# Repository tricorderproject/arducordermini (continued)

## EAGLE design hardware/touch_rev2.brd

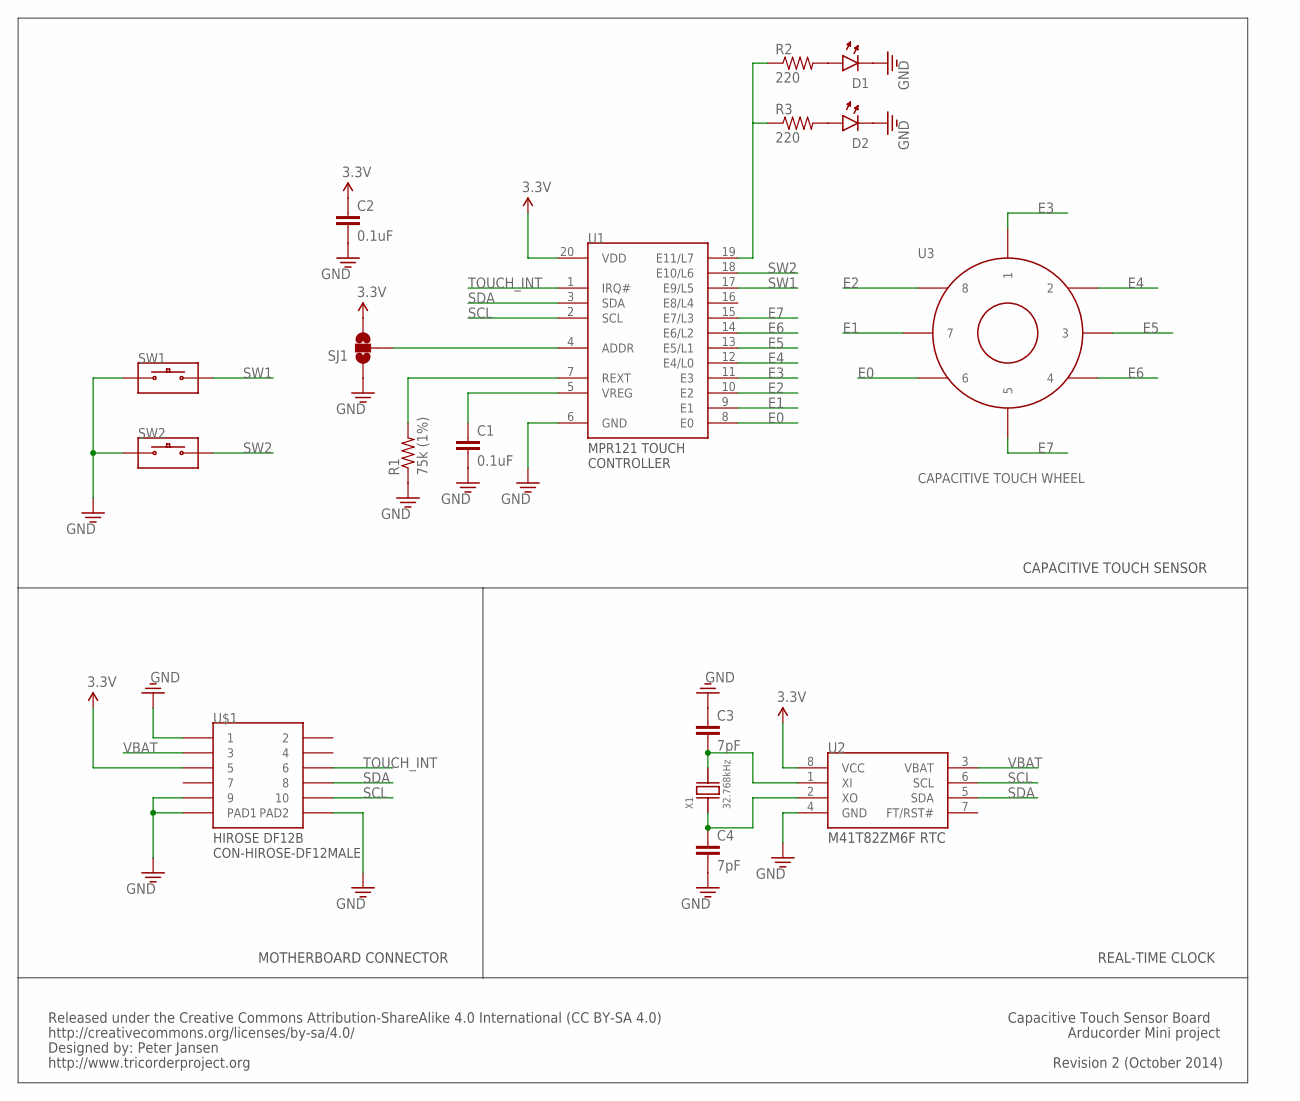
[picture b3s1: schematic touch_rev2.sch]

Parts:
C1, C2: 0.1uF; 0603
C3, C4: 7pF; 0603
D1, D2: 0605-LED; 0603-LED
R1: 75k (1%); 0603
R2, R3: 220; 0603
SJ1: SOLDERJUMPER_2WAYPASTE1&2; SJ_3_PASTE1&2
SW1, SW2: SWITCH; KMT071
U1: MPR121-TOUCH-CONTROLLER; QFN-3X3-20
U2: M41T82ZM6F; 8-SOIC
U3: CAPACITIVE-WHEEL-8
U$1: CON-HIROSE-DF12MALE; DF12B(3.0)-10DS-0.5V(86)
X1: 32.768kHz; CRYSTAL-9HT10

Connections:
3.3V: C2.1, SJ1.3, U1.20 (VDD), U2.8 (VCC), U$1.5
E0: U1.8 (E0), U3.6
E1: U1.9 (E1), U3.7
E2: U1.10 (E2), U3.8
E3: U1.11 (E3), U3.1
E4: U1.12 (E4/L0), U3.2
E5: U1.13 (E5/L1), U3.3
E6: U1.14 (E6/L2), U3.4
E7: U1.15 (E7/L3), U3.5
GND: C1.2, C2.2, C3.1, C4.2, D1.CATHODE, D2.CATHODE, R1.1, SJ1.1, SW1.1A, SW2.1A, U1.6 (GND), U2.4 (GND), U$1.1, U$1.9, U$1.PAD1, U$1.PAD2
unnamed: D1.ANODE, R2.2
unnamed: D2.ANODE, R3.2
unnamed: C1.1, U1.5 (VREG)
unnamed: R1.2, U1.7 (REXT)
unnamed: SJ1.2, U1.4 (ADDR)
unnamed: R2.1, R3.1, U1.19 (E11/L7)
unnamed: C4.1, U2.2 (XO), X1.1
unnamed: C3.2, U2.1 (XI), X1.2
SCL: U1.2 (SCL), U2.6 (SCL), U$1.10
SDA: U1.3 (SDA), U2.5 (SDA), U$1.8
SW1: SW1.2A, U1.17 (E9/L5)
SW2: SW2.2A, U1.18 (E10/L6)
TOUCH_INT: U1.1 (IRQ#), U$1.6
VBAT: U2.3 (VBAT), U$1.3

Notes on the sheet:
CAPACITIVE TOUCH SENSOR
REAL-TIME CLOCK
MOTHERBOARD CONNECTOR
Released under the Creative Commons Attribution-ShareAlike 4.0 International (CC BY-SA 4.0)
http://creativecommons.org/licenses/by-sa/4.0/
Designed by: Peter Jansen
http://www.tricorderproject.org
Revision 2 (October 2014)
Arducorder Mini project
Capacitive Touch Sensor Board

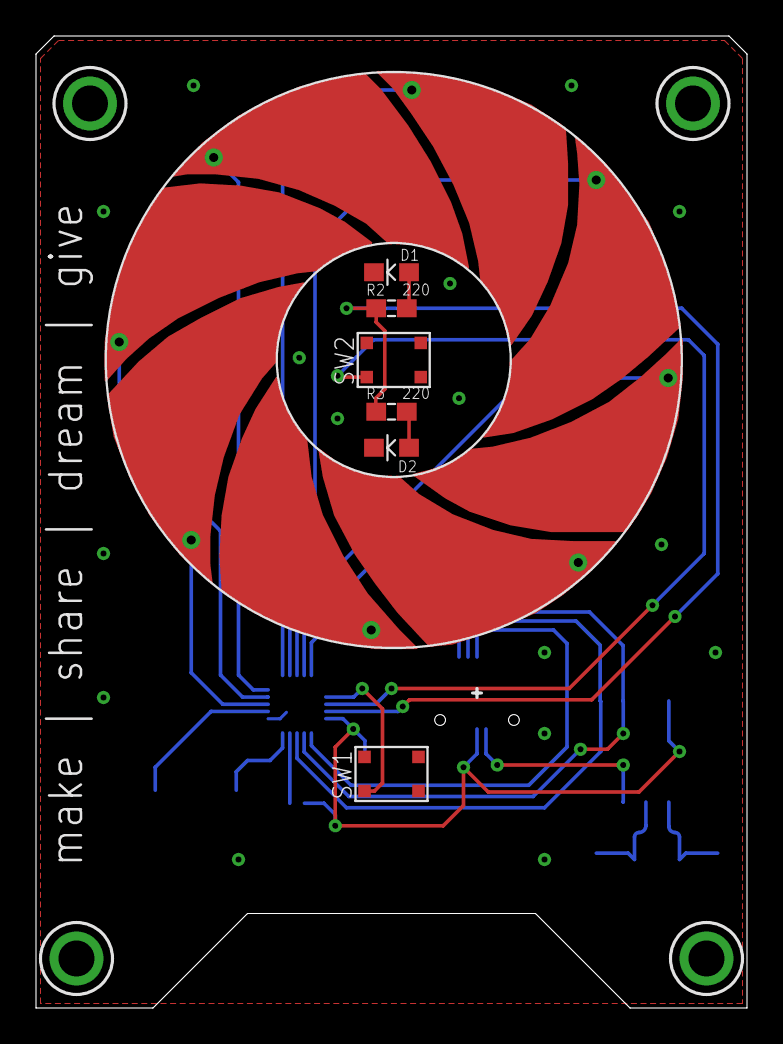
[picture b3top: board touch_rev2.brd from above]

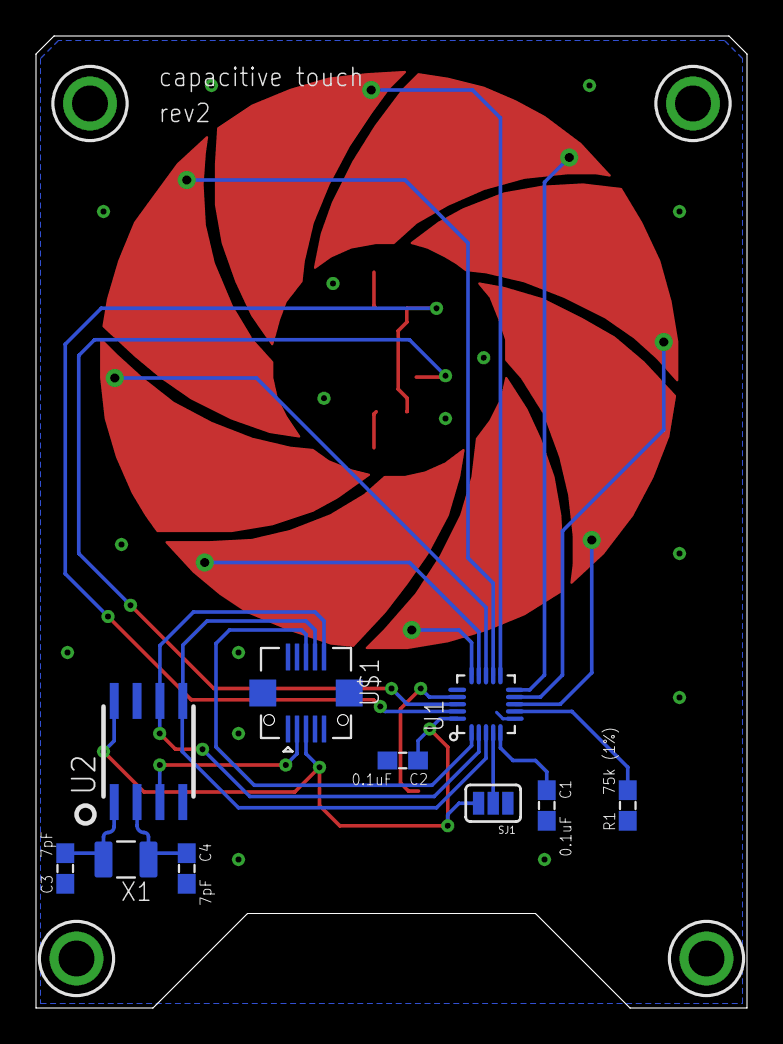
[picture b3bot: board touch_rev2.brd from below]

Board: 2 copper layers, 39.5 x 54.0 mm, 17 parts (9 on the bottom side), 24 nets.

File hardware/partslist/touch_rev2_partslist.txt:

Partlist

Exported from touch_rev2.sch at 27/10/2014 11:53:52 PM

EAGLE Version 6.5.0 Copyright (c) 1988-2013 CadSoft

Assembly variant: 

Part     Value                   Device                    Package                  Library               Sheet

C1       0.1uF                   CAP0603                   0603                     notes_mark5a          1
C2       0.1uF                   CAP0603                   0603                     notes_mark5a          1
C3       7pF                     CAP0603                   0603                     notes_mark5a          1
C4       7pF                     CAP0603                   0603                     notes_mark5a          1
D1       0605-LED                0605-LED                  0603-LED                 notes_mark5a1         1
D2       0605-LED                0605-LED                  0603-LED                 notes_mark5a1         1
R1       75k (1%)                RESISTOR0603              0603                     notes_mark5a1         1
R2       220                     RESISTOR0603              0603                     notes_mark5a1         1
R3       220                     RESISTOR0603              0603                     notes_mark5a1         1
SJ1                              SOLDERJUMPER_2WAYPASTE1&2 SJ_3_PASTE1&2            SparkFun-Passives     1
SW1      SWITCH                  SWITCH                    KMT071                   notes-arducorder-mini 1
SW2      SWITCH                  SWITCH                    KMT071                   notes-arducorder-mini 1
U$1      CON-HIROSE-DF12MALE     CON-HIROSE-DF12MALE       DF12B(3.0)-10DS-0.5V(86) arducorder-mini       1
U1       MPR121-TOUCH-CONTROLLER MPR121-TOUCH-CONTROLLER   QFN-3X3-20               notes-arducorder-mini 1
U2       M41T82ZM6F              M41T82ZM6F                8-SOIC                   notes_mark5a          1
U3       CAPACITIVE-WHEEL-8      CAPACITIVE-WHEEL-8        CAPACITIVE-WHEEL-8       notes-arducorder-mini 1
X1       32.768kHz               CRYSTAL                   CRYSTAL-9HT10            notes_mark5a          1

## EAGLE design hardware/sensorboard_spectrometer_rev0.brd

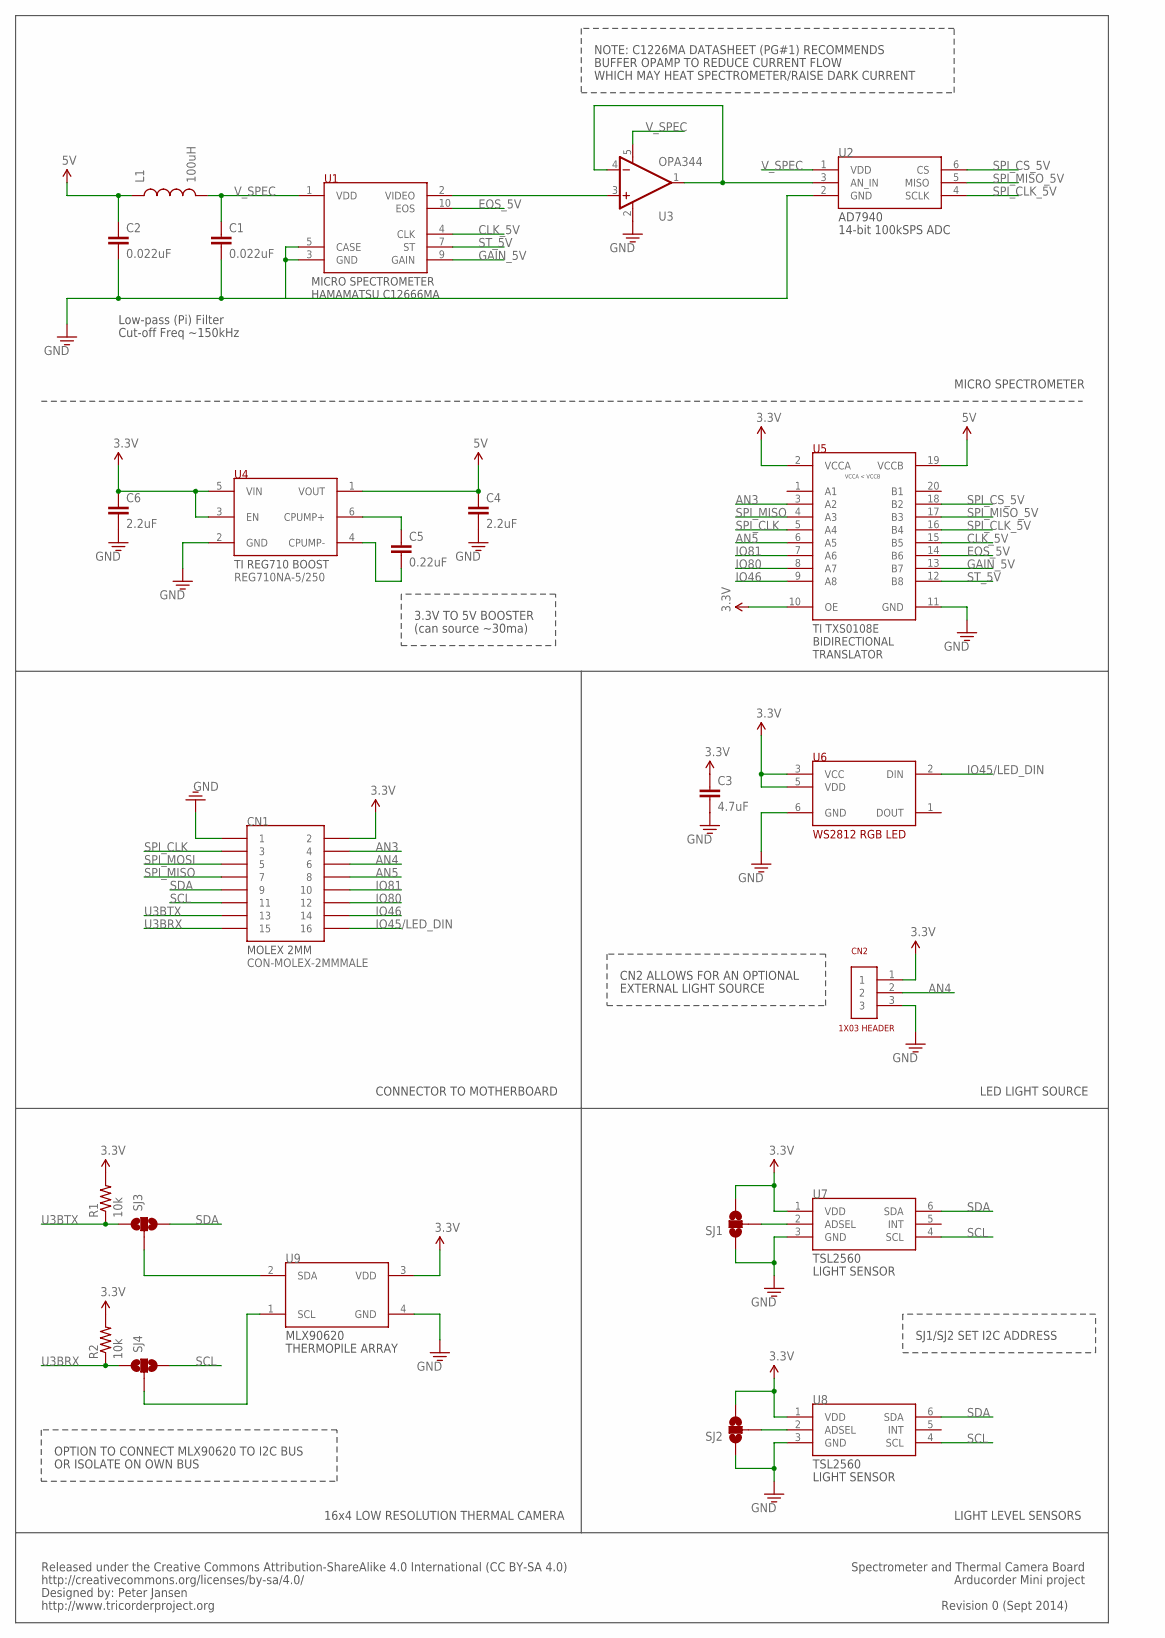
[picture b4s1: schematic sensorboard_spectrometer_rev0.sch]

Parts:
C1, C2: 0.022uF; 0603
C3: 4.7uF; 0603
C4, C6: 2.2uF; 0603
C5: 0.22uF; 0603
CN1: CON-MOLEX-2MMMALE; MOLEX-0877591650
CN2: 1X03
L1: 100uH; 0805
R1, R2: 10k; 0603
SJ1, SJ3, SJ4: SOLDERJUMPER_2WAYPASTE1&2; SJ_3_PASTE1&2
SJ2: SOLDERJUMPER_2WAYPASTE2&3; SJ_3_PASTE2&3
U1: MICROSPEC-C12666MA; C12666MA
U2: AD7940; SOT-23-6L
U3: OPA344; SOT23-5
U4: REG710NA-5/250; SOT-23-6L
U5: TRANSLATOR-TXS0108E; TSSOP-20
U6: WS2812_NEOPIXEL; WS2812
U7, U8: TSL2561; TMB-6
U9: MLX90620

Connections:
3.3V: C3.1, C6.1, CN1.2, CN2.1, R1.2, R2.2, SJ1.3, SJ2.3, U4.3 (EN), U4.5 (VIN), U5.2 (VCCA), U5.10 (OE), U6.3 (VCC), U6.5 (VDD), U7.1 (VDD), U8.1 (VDD), U9.3 (VDD)
5V: C2.1, C4.1, L1.1, U4.1 (VOUT), U5.19 (VCCB)
AN3: CN1.4, U5.3 (A2)
AN4: CN1.6, CN2.2
AN5: CN1.8, U5.6 (A5)
CLK_5V: U1.4 (CLK), U5.15 (B5)
EOS_5V: U1.10 (EOS), U5.14 (B6)
GAIN_5V: U1.9 (GAIN), U5.13 (B7)
GND: C1.2, C2.2, C3.2, C4.2, C6.2, CN1.1, CN2.3, SJ1.1, SJ2.1, U1.3 (GND), U1.5 (CASE), U2.2 (GND), U3.2 (V-), U4.2 (GND), U5.11 (GND), U6.6 (GND), U7.3 (GND), U8.3 (GND), U9.4 (GND)
IO45/LED_DIN: CN1.16, U6.2 (DIN)
IO46: CN1.14, U5.9 (A8)
IO80: CN1.12, U5.8 (A7)
IO81: CN1.10, U5.7 (A6)
unnamed: U2.3 (AN_IN), U3.1 (OUT), U3.4 (-IN)
unnamed: U1.2 (VIDEO), U3.3 (+IN)
unnamed: SJ2.2, U8.2 (ADSEL)
unnamed: SJ1.2, U7.2 (ADSEL)
unnamed: C5.1, U4.6 (CPUMP+)
unnamed: C5.2, U4.4 (CPUMP-)
unnamed: SJ4.2, U9.1 (SCL)
unnamed: SJ3.2, U9.2 (SDA)
SCL: CN1.11, SJ4.3, U7.4 (SCL), U8.4 (SCL)
SDA: CN1.9, SJ3.3, U7.6 (SDA), U8.6 (SDA)
SPI_CLK: CN1.3, U5.5 (A4)
SPI_CLK_5V: U2.4 (SCLK), U5.16 (B4)
SPI_CS_5V: U2.6 (CS), U5.18 (B2)
SPI_MISO: CN1.7, U5.4 (A3)
SPI_MISO_5V: U2.5 (MISO), U5.17 (B3)
SPI_MOSI: CN1.5
ST_5V: U1.7 (ST), U5.12 (B8)
U3BRX: CN1.15, R2.1, SJ4.1
U3BTX: CN1.13, R1.1, SJ3.1
V_SPEC: C1.1, L1.2, U1.1 (VDD), U2.1 (VDD), U3.5 (V+)

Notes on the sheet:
Low-pass (Pi) Filter
Cut-off Freq ~150kHz
CONNECTOR TO MOTHERBOARD
LED LIGHT SOURCE
16x4 LOW RESOLUTION THERMAL CAMERA
LIGHT LEVEL SENSORS
3.3V TO 5V BOOSTER
(can source ~30ma)
MICRO SPECTROMETER
NOTE: C1226MA DATASHEET (PG#1) RECOMMENDS
BUFFER OPAMP TO REDUCE CURRENT FLOW
WHICH MAY HEAT SPECTROMETER/RAISE DARK CURRENT
CN2 ALLOWS FOR AN OPTIONAL
EXTERNAL LIGHT SOURCE
OPTION TO CONNECT MLX90620 TO I2C BUS
OR ISOLATE ON OWN BUS
SJ1/SJ2 SET I2C ADDRESS
Released under the Creative Commons Attribution-ShareAlike 4.0 International (CC BY-SA 4.0)
http://creativecommons.org/licenses/by-sa/4.0/
Designed by: Peter Jansen
http://www.tricorderproject.org
Revision 0 (Sept 2014)
Arducorder Mini project
Spectrometer and Thermal Camera Board

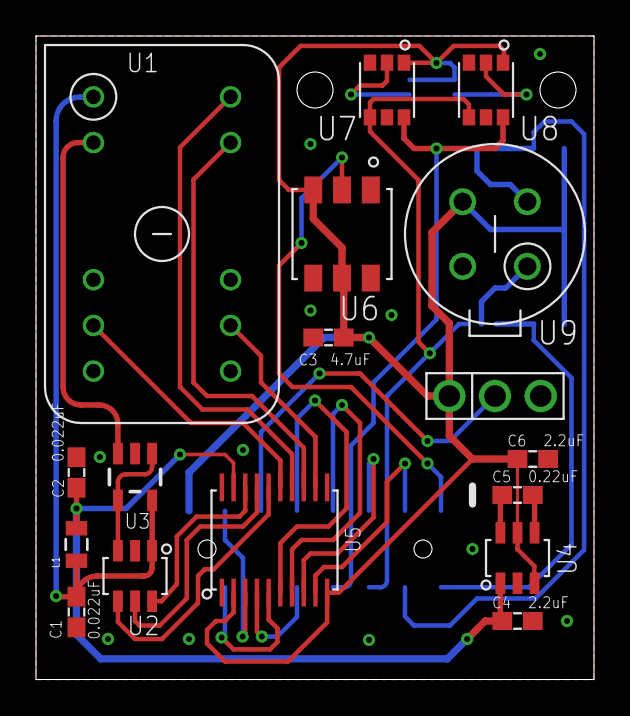
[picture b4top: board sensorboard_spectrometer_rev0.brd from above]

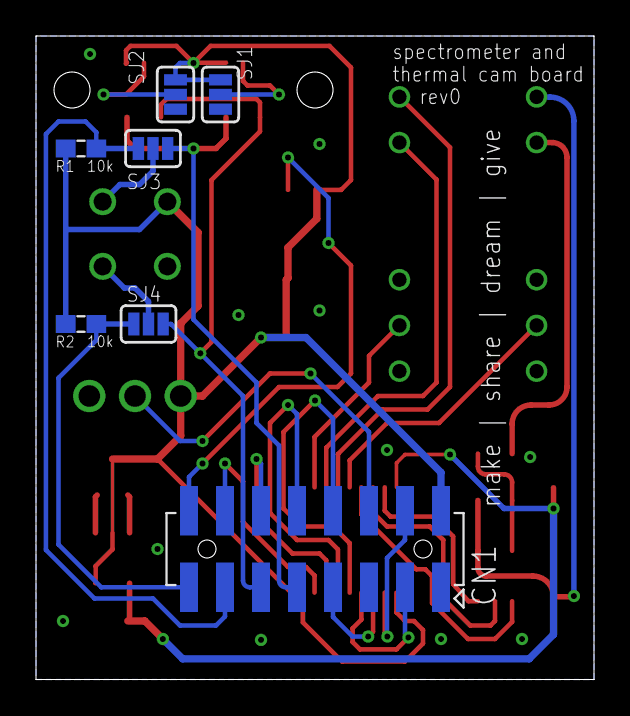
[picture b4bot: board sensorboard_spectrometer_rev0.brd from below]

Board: 2 copper layers, 31.0 x 35.8 mm, 24 parts (7 on the bottom side), 32 nets.

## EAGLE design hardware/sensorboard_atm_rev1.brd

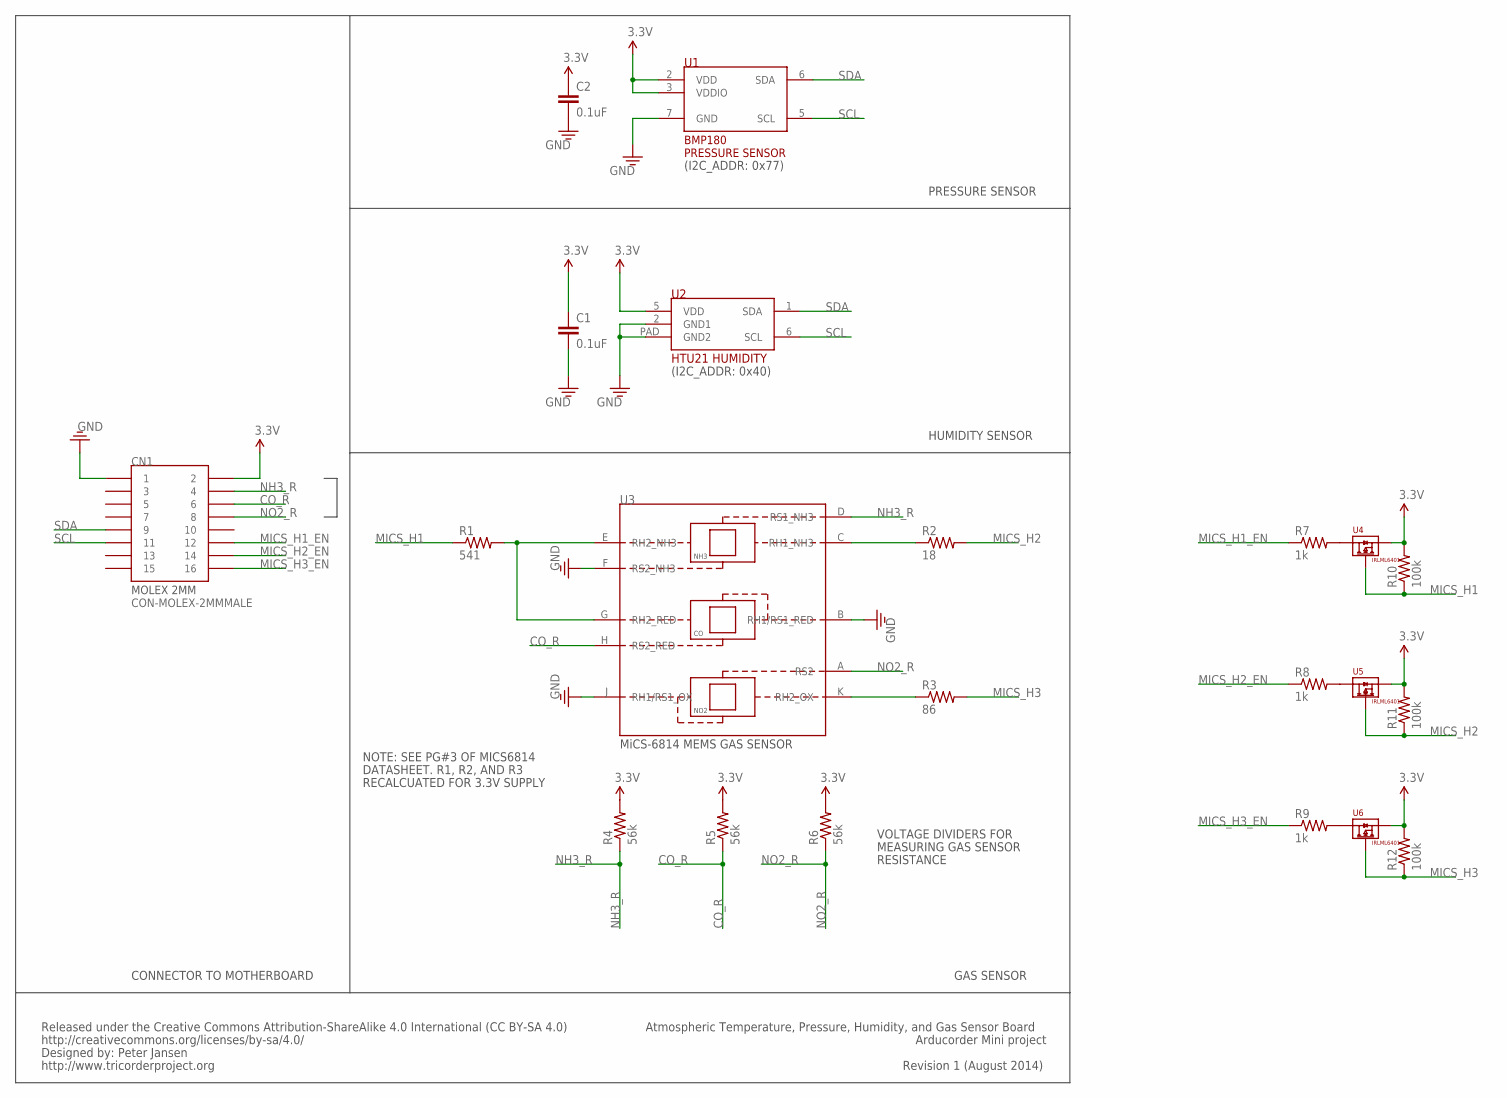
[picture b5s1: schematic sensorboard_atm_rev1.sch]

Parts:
C1, C2: 0.1uF; 0603
CN1: CON-MOLEX-2MMMALE; MOLEX-0877591650
R1: 541; 0603
R2: 18; 0603
R3: 86; 0603
R4, R5, R6: 56k; 0603
R7, R8, R9: 1k; 0603
R10, R11, R12: 100k; 0603
U1: BMP180
U2: HTU21D
U3: MICS-6814
U4, U5, U6: MOSFET-IRLML6401; SOT23-3L

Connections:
3.3V: C1.1, C2.1, CN1.2, R4.2, R5.2, R6.2, R10.2, R11.2, R12.2, U1.2 (VDD), U1.3 (VDDIO), U2.5 (VDD), U4.2 (S), U5.2 (S), U6.2 (S)
CO_R: CN1.6, R5.1, U3.H (RS2_RED)
GND: C1.2, C2.2, CN1.1, U1.7 (GND), U2.2 (GND1), U2.PAD (GND2), U3.B (RH1/RS1_RED), U3.F (RS2_NH3), U3.J (RH1/RS1_OX)
MICS_H1: R1.1, R10.1, U4.1 (G)
MICS_H1_EN: CN1.12, R7.1
MICS_H2: R2.2, R11.1, U5.1 (G)
MICS_H2_EN: CN1.14, R8.1
MICS_H3: R3.2, R12.1, U6.1 (G)
MICS_H3_EN: CN1.16, R9.1
unnamed: R7.2, U4.3 (D)
unnamed: R8.2, U5.3 (D)
unnamed: R9.2, U6.3 (D)
unnamed: R1.2, U3.E (RH2_NH3), U3.G (RH2_RED)
unnamed: R2.1, U3.C (RH1_NH3)
unnamed: R3.1, U3.K (RH2_OX)
NH3_R: CN1.4, R4.1, U3.D (RS1_NH3)
NO2_R: CN1.8, R6.1, U3.A (RS2)
SCL: CN1.11, U1.5 (SCL), U2.6 (SCL)
SDA: CN1.9, U1.6 (SDA), U2.1 (SDA)

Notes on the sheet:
(I2C_ADDR: 0x77)
VOLTAGE DIVIDERS FOR
MEASURING GAS SENSOR
RESISTANCE
(I2C_ADDR: 0x40)
Released under the Creative Commons Attribution-ShareAlike 4.0 International (CC BY-SA 4.0)
http://creativecommons.org/licenses/by-sa/4.0/
Designed by: Peter Jansen
http://www.tricorderproject.org
Revision 1 (August 2014)
Arducorder Mini project
Atmospheric Temperature, Pressure, Humidity, and Gas Sensor Board
CONNECTOR TO MOTHERBOARD
NOTE: SEE PG#3 OF MICS6814
DATASHEET. R1, R2, AND R3
RECALCUATED FOR 3.3V SUPPLY
GAS SENSOR
HUMIDITY SENSOR
PRESSURE SENSOR

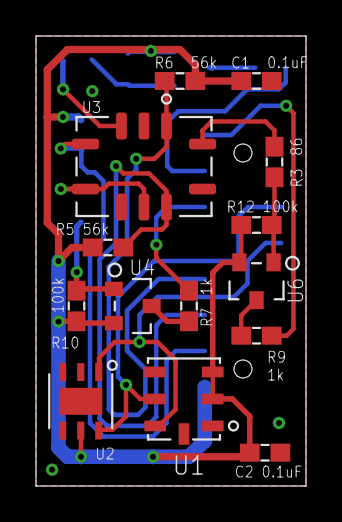
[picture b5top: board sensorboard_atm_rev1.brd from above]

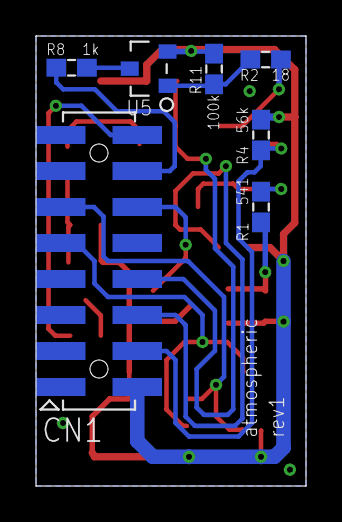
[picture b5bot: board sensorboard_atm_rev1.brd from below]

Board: 2 copper layers, 15.0 x 25.0 mm, 21 parts (7 on the bottom side), 19 nets.

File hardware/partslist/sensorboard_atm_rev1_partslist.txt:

Partlist

Exported from sensorboard_atm_rev1.sch at 27/10/2014 11:52:27 PM

EAGLE Version 6.5.0 Copyright (c) 1988-2013 CadSoft

Assembly variant: 

Part     Value             Device            Package          Library               Sheet

C1       0.1uF             CAP0603           0603             notes_mark5a          1
C2       0.1uF             CAP0603           0603             notes_mark5a          1
CN1      CON-MOLEX-2MMMALE CON-MOLEX-2MMMALE MOLEX-0877591650 notes-arducorder-mini 1
R1       541               RESISTOR0603      0603             notes_mark5a          1
R2       18                RESISTOR0603      0603             notes_mark5a          1
R3       86                RESISTOR0603      0603             notes_mark5a          1
R4       56k               RESISTOR0603      0603             notes_mark5a          1
R5       56k               RESISTOR0603      0603             notes_mark5a          1
R6       56k               RESISTOR0603      0603             notes_mark5a          1
R7       1k                RESISTOR0603      0603             notes_mark5a          1
R8       1k                RESISTOR0603      0603             notes_mark5a          1
R9       1k                RESISTOR0603      0603             notes_mark5a          1
R10      100k              RESISTOR0603      0603             notes_mark5a          1
R11      100k              RESISTOR0603      0603             notes_mark5a          1
R12      100k              RESISTOR0603      0603             notes_mark5a          1
U1       BMP180            BMP180            BMP180           notes_mark5a          1
U2       HTU21D            HTU21D            HTU21D           notes_mark5a          1
U3       MICS-6814         MICS-6814         MICS-6814        notes_mark5a          1
U4       MOSFET-IRLML6401  MOSFET-IRLML6401  SOT23-3L         arducorder-mini       1
U5       MOSFET-IRLML6401  MOSFET-IRLML6401  SOT23-3L         arducorder-mini       1
U6       MOSFET-IRLML6401  MOSFET-IRLML6401  SOT23-3L         arducorder-mini       1

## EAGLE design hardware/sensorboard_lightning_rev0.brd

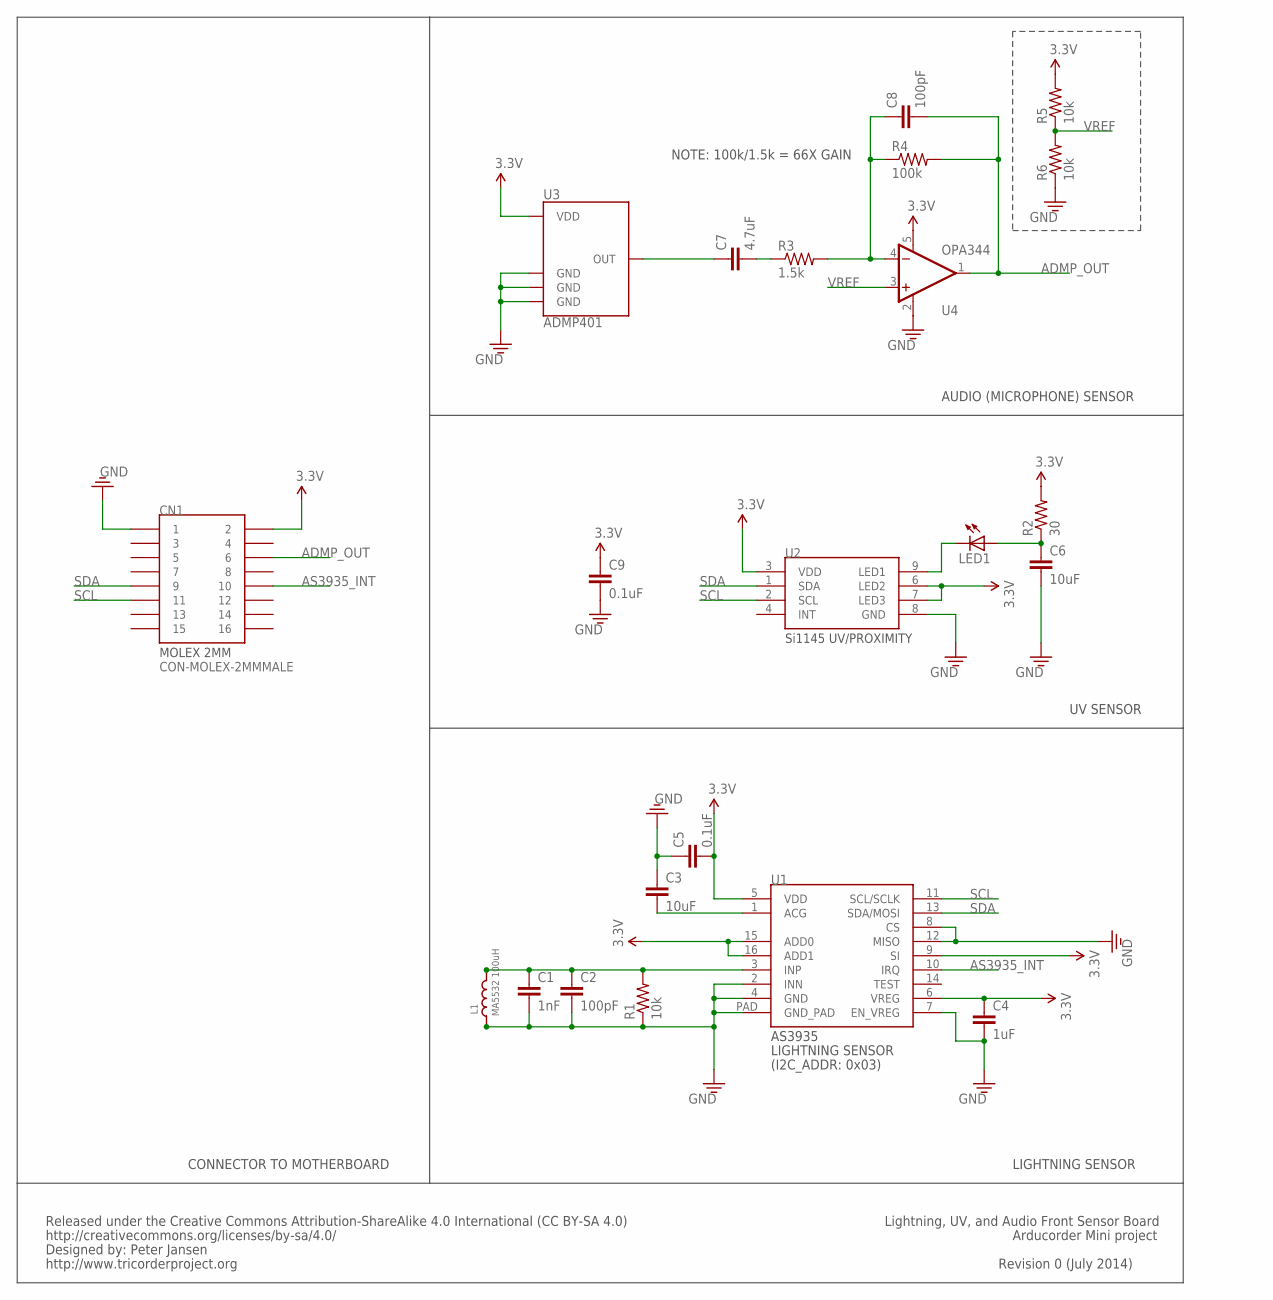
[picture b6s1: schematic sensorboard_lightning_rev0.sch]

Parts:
C1: 1nF; 0603
C2, C8: 100pF; 0603
C3, C6: 10uF; 0603
C4: 1uF; 0603
C5, C9: 0.1uF; 0603
C7: 4.7uF; 0603
CN1: CON-MOLEX-2MMMALE; MOLEX-0877591650
L1: MA5532 100uH; MA5532-AE
LED1: LED1206; LED-1206
R1, R5, R6: 10k; 0603
R2: 30; 0603
R3: 1.5k; 0603
R4: 100k; 0603
U1: AS3935; 16LD_MLPQ-(4X4MM)
U2: SI1145
U3: ADMP401
U4: OPA344; SOT23-5

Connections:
3.3V: C4.1, C5.2, C9.1, CN1.2, R2.2, R5.2, U1.5 (VDD), U1.6 (VREG), U1.9 (SI), U1.15 (ADD0), U1.16 (ADD1), U2.3 (VDD), U2.6 (LED2), U2.7 (LED3), U3.5 (VDD), U4.5 (V+)
ADMP_OUT: C8.2, CN1.6, R4.2, U4.1 (OUT)
AS3935_INT: CN1.10, U1.10 (IRQ)
GND: C1.2, C2.2, C3.1, C4.2, C5.1, C6.2, C9.2, CN1.1, L1.2, R1.1, R6.1, U1.2 (INN), U1.4 (GND), U1.7 (EN_VREG), U1.8 (CS), U1.12 (MISO), U1.PAD (GND_PAD), U2.8 (GND), U3.2 (GND), U3.4 (GND), U3.6 (GND), U4.2 (V-)
unnamed: LED1.C, U2.9 (LED1)
unnamed: C3.2, U1.1 (ACG)
unnamed: C6.1, LED1.A, R2.1
unnamed: C1.1, C2.1, L1.1, R1.2, U1.3 (INP)
unnamed: C7.2, R3.1
unnamed: C8.1, R3.2, R4.1, U4.4 (-IN)
unnamed: C7.1, U3.1 (OUT)
SCL: CN1.11, U1.11 (SCL/SCLK), U2.2 (SCL)
SDA: CN1.9, U1.13 (SDA/MOSI), U2.1 (SDA)
VREF: R5.1, R6.2, U4.3 (+IN)

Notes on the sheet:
(I2C_ADDR: 0x03)
Released under the Creative Commons Attribution-ShareAlike 4.0 International (CC BY-SA 4.0)
http://creativecommons.org/licenses/by-sa/4.0/
Designed by: Peter Jansen
http://www.tricorderproject.org
Revision 0 (July 2014)
Arducorder Mini project
Lightning, UV, and Audio Front Sensor Board
CONNECTOR TO MOTHERBOARD
LIGHTNING SENSOR
UV SENSOR
AUDIO (MICROPHONE) SENSOR
NOTE: 100k/1.5k = 66X GAIN

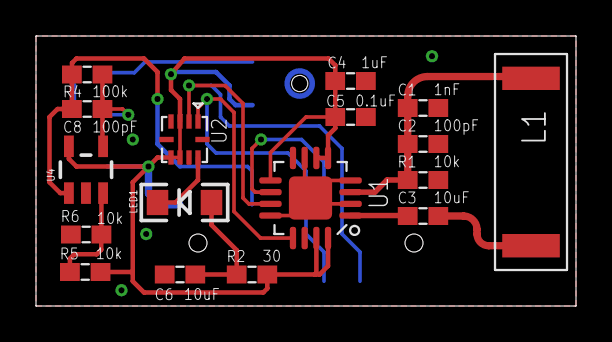
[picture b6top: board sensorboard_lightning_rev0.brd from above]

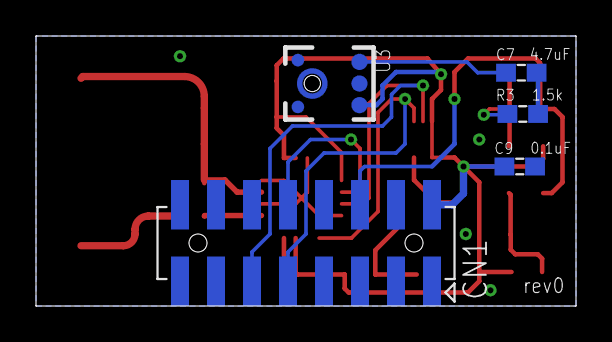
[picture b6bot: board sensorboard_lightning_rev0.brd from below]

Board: 2 copper layers, 30.0 x 15.0 mm, 22 parts (5 on the bottom side), 14 nets.

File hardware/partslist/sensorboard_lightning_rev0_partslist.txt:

Partlist

Exported from sensorboard_lightning_rev0.sch at 27/10/2014 11:52:52 PM

EAGLE Version 6.5.0 Copyright (c) 1988-2013 CadSoft

Assembly variant: 

Part     Value             Device            Package           Library               Sheet

C1       1nF               CAP0603           0603              notes_mark5           1
C2       100pF             CAP0603           0603              notes_mark5           1
C3       10uF              CAP0603           0603              notes_mark5           1
C4       1uF               CAP0603           0603              notes_mark5           1
C5       0.1uF             CAP0603           0603              notes_mark5           1
C6       10uF              CAP0603           0603              notes_mark5           1
C7       4.7uF             CAP0603           0603              notes_mark5a          1
C8       100pF             CAP0603           0603              notes_mark5a          1
C9       0.1uF             CAP0603           0603              notes_mark5           1
CN1      CON-MOLEX-2MMMALE CON-MOLEX-2MMMALE MOLEX-0877591650  notes-arducorder-mini 1
L1       MA5532 100uH      INDUCTOR          MA5532-AE         notes_mark5           1
LED1                       LED1206           LED-1206          SparkFun-LED          1
R1       10k               RESISTOR0603      0603              notes_mark5           1
R2       30                RESISTOR0603      0603              notes_mark5           1
R3       1.5k              RESISTOR0603      0603              notes_mark5a          1
R4       100k              RESISTOR0603      0603              notes_mark5a          1
R5       10k               RESISTOR0603      0603              notes_mark5a          1
R6       10k               RESISTOR0603      0603              notes_mark5a          1
U1       AS3935            AS3935            16LD_MLPQ-(4X4MM) notes_mark5           1
U2       SI1145            SI1145            SI1145            notes-arducorder-mini 1
U3       ADMP401           ADMP401           ADMP401           SparkFun-Sensors      1
U4       OPA344            OPA344            SOT23-5           SparkFun-AnalogIC     1

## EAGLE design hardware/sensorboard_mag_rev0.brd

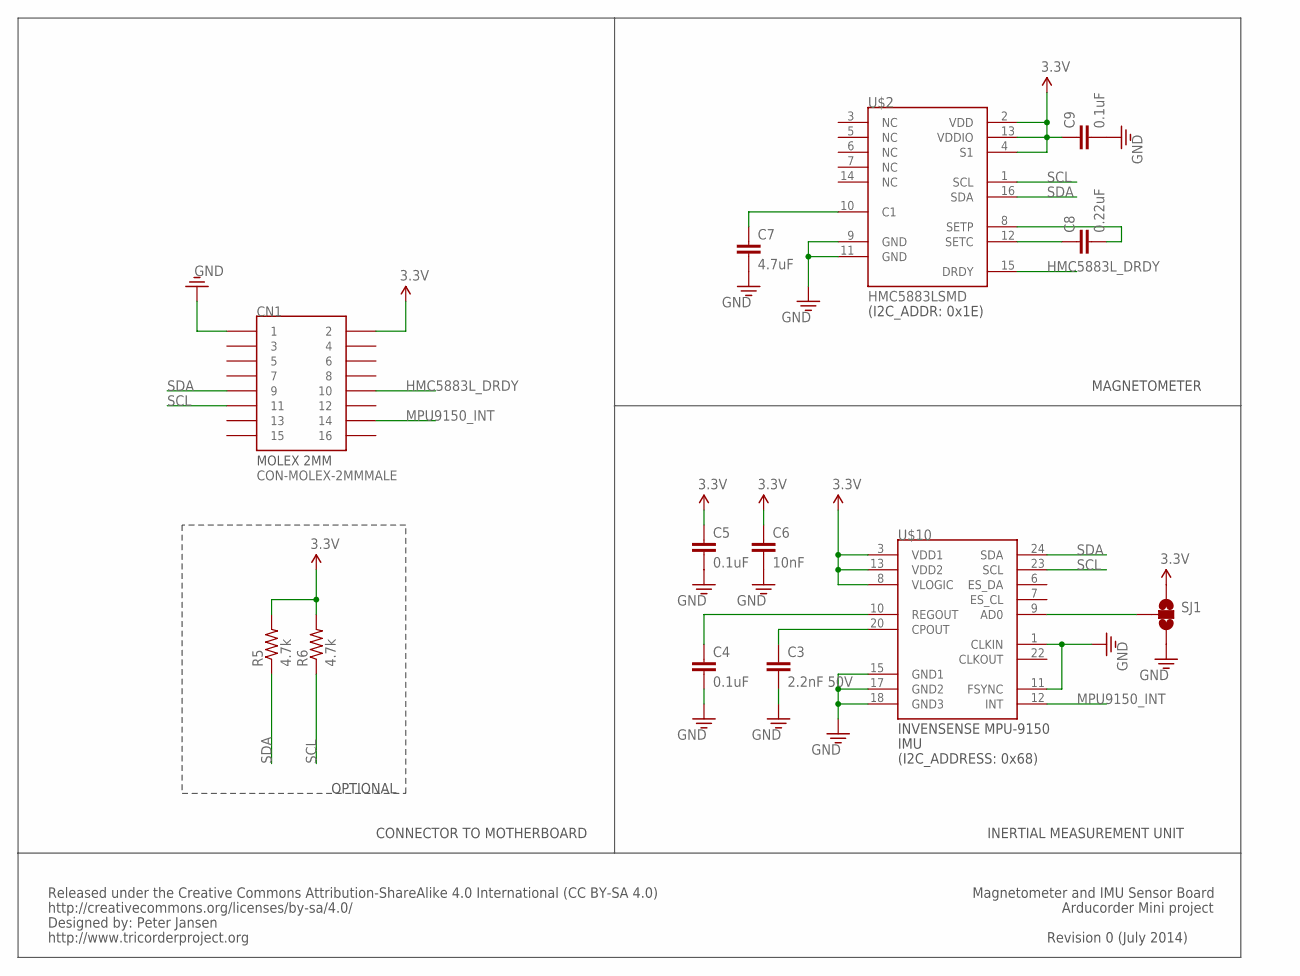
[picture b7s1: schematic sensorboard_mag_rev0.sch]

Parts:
C3: 2.2nF 50V; 0603
C4, C5, C9: 0.1uF; 0603
C6: 10nF; 0603
C7: 4.7uF; 0603
C8: 0.22uF; 0603
CN1: CON-MOLEX-2MMMALE; MOLEX-0877591650
R5, R6: 4.7k; 0603
SJ1: SOLDERJUMPER_2WAYPASTE2&3; SJ_3_PASTE2&3
U$2: HMC5883LSMD; 16LPCC
U$10: MPU-9150; LGA-24-(4X4MM)

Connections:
3.3V: C5.1, C6.1, C9.1, CN1.2, R5.2, R6.2, SJ1.1, U$2.2 (VDD), U$2.4 (S1), U$2.13 (VDDIO), U$10.3 (VDD1), U$10.8 (VLOGIC), U$10.13 (VDD2)
GND: C3.2, C4.2, C5.2, C6.2, C7.2, C9.2, CN1.1, SJ1.3, U$2.9 (GND), U$2.11 (GND), U$10.1 (CLKIN), U$10.11 (FSYNC), U$10.15 (GND1), U$10.17 (GND2), U$10.18 (GND3)
HMC5883L_DRDY: CN1.10, U$2.15 (DRDY)
MPU9150_INT: CN1.14, U$10.12 (INT)
unnamed: SJ1.2, U$10.9 (AD0)
unnamed: C7.1, U$2.10 (C1)
unnamed: C3.1, U$10.20 (CPOUT)
unnamed: C4.1, U$10.10 (REGOUT)
unnamed: C8.1, U$2.12 (SETC)
unnamed: C8.2, U$2.8 (SETP)
SCL: CN1.11, R6.1, U$2.1 (SCL), U$10.23 (SCL)
SDA: CN1.9, R5.1, U$2.16 (SDA), U$10.24 (SDA)

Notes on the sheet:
(I2C_ADDRESS: 0x68)
(I2C_ADDR: 0x1E)
Released under the Creative Commons Attribution-ShareAlike 4.0 International (CC BY-SA 4.0)
http://creativecommons.org/licenses/by-sa/4.0/
Designed by: Peter Jansen
http://www.tricorderproject.org
Revision 0 (July 2014)
Arducorder Mini project
Magnetometer and IMU Sensor Board
INERTIAL MEASUREMENT UNIT
MAGNETOMETER
OPTIONAL
CONNECTOR TO MOTHERBOARD

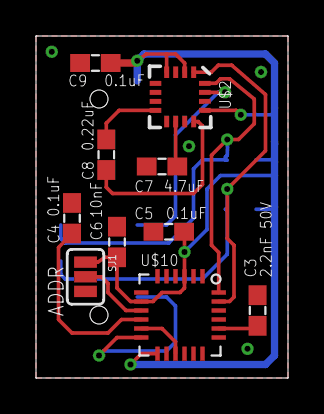
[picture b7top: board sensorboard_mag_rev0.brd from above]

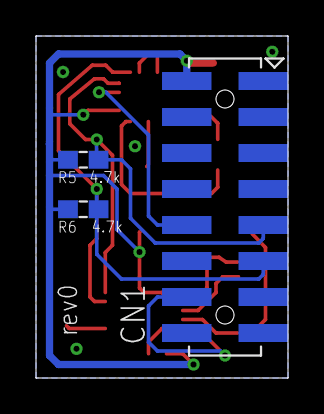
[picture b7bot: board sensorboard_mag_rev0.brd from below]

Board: 2 copper layers, 14.0 x 19.0 mm, 13 parts (3 on the bottom side), 12 nets.

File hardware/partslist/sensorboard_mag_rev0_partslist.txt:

Partlist

Exported from sensorboard_mag_rev0.sch at 27/10/2014 11:53:09 PM

EAGLE Version 6.5.0 Copyright (c) 1988-2013 CadSoft

Assembly variant: 

Part     Value             Device                    Package          Library               Sheet

C3       2.2nF 50V         CAP0603                   0603             notes_mark5           1
C4       0.1uF             CAP0603                   0603             notes_mark5           1
C5       0.1uF             CAP0603                   0603             notes_mark5           1
C6       10nF              CAP0603                   0603             notes_mark5           1
C7       4.7uF             CAP0603                   0603             notes_mark5           1
C8       0.22uF            CAP0603                   0603             notes_mark5           1
C9       0.1uF             CAP0603                   0603             notes_mark5           1
CN1      CON-MOLEX-2MMMALE CON-MOLEX-2MMMALE         MOLEX-0877591650 notes-arducorder-mini 1
R5       4.7k              RESISTOR0603              0603             notes_mark5a          1
R6       4.7k              RESISTOR0603              0603             notes_mark5a          1
SJ1                        SOLDERJUMPER_2WAYPASTE2&3 SJ_3_PASTE2&3    SparkFun-Passives     1
U$2      HMC5883LSMD       HMC5883LSMD               16LPCC           SparkFun-Sensors      1
U$10     MPU-9150          MPU-9150                  LGA-24-(4X4MM)   notes_mark5           1

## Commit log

2014-08-11 README
2014-08-11 ERRATA
2014-08-11 minor changeS
2014-08-16 Added initial hardware source files
2014-08-17 Added test firmware in it's current state
2014-08-26 Added revision 1 of the atmospheric sensor board, with MOSFETs for the MiCS6814 gas sensor
2014-09-01 Added spectrometer and thermal camera board (rev0)
2014-09-01 Added note after testing audio
2014-09-04 Added spectrometer sensor board gerbers
2014-09-04 Added image posterizing tool for Processing
2014-09-06 Added initial font renderer and Processing font conversion tool
2014-09-06 Added Ubuntu font license text
2014-09-07 added gradientRect() to Framebuffer Graphics Library
2014-09-07 Small bug fix in font renderer -- sizeX and sizeY were off by 1, cutting off the corners of each letter.
2014-09-07 Added Ubuntu Condensed font
2014-09-08 minor changes - fonts
2014-09-08 Changed FontConverter to export fonts as constant arrays. Also started tile system.
2014-09-08 Added initial tile classes
2014-09-10 Changes to font renderer: bug fix in textLength, added drawJustifiedText function for easy formatting
2014-09-11 Refactored the flash bitmaps into a const structure, modified posterizer tool to export that structure, and added a few quick test bitmaps for the tile symbols
2014-09-11 Two test tiles
2014-09-11 Fixed bug in font renderer for center-justified text
2014-09-11 Beginning construction of Tile GUI component
2014-09-12 Added prototype automated tile packer for TileGUI
2014-09-14 Added more to basic tile interface: Added most initial tiles, bitmaps for tiles, symbol artwork, refactored tile packing mechanism and tile GUI, added mechanism to scroll through tiles
2014-09-14 Added visual tile page counter on the bottom of the tile navigation screen
2014-09-14 Added descretized scroll wheel functionality for incrementing/decrementing a value
2014-09-19 Minor change -- SensorBuffer now has a function to return the most recently stored value, and the Tile constructor now accepts a SensorBuffer pointer that it can draw data from
2014-09-24 Added lightweight MLX90620 library
2014-09-25 Added live bitmap for the thermal imager tile
2014-09-25 fixing bugs (uninitialised variable in RGB(), posterised bitmaps weren't writing to left and top lines)
2014-09-25 added huffman-encoded bitmap loader'
2014-09-25 added drawPixel() with alpha blending
2014-09-25 Added Hue (HSB) to RGB converter, and temperature-based color map
2014-09-26 Added C12666MA micro spectrometer driver
2014-09-26 Added spectrometer live graph tile -- still some bugs to work out
2014-09-26 Fixed issues with spectrometer tile -- SensorBuffer is statically sized, so had to resample spectrometer data to buffer size in populateSensorBuffer(). Result is too cool!
2014-09-27 Added interrupt-based driver for Radiation Watch type 5
2014-09-27 Improvements to tile interface
2014-09-27 minor changes to tile interface
2014-09-27 Updated MPR121 library to detect pushbuttons. Currently detects buttons using capacitance instead of the GPIO library
2014-09-27 Refactoring to incorporate graph view
2014-09-27 Transition from tile to graph-based interface is working with select/back buttons
2014-09-27 Enhancements to graph view
2014-09-30 Added modified ChipKit IDE with updated peripheral libraries, and Adafruit CC3000 library ported to Chipkit
2014-09-30 Added modified Chipkit IDE as separate files. I tried to add it as an archive last night, and github rejected the archive as too large
2014-10-07 Added revision 1 to motherboard, as well as CHANGELOG file
2014-10-07 Added capacitive touch board, revision 2, which moves most of the parts to the bottom of the board, adds mounting holes, and matches the motherboard rev1 footprint
2014-10-08 Added motherboard rev1 and capacitive touch board rev2
2014-10-09 Added radiation sensor board rev1
2014-10-23 Change to capacitive touch wheel calibration for acrylic faceplate. Minor bugfix for thermal display tile
2014-10-23 Code for Si1145 UV sensor enabled and working
2014-10-24 Added plotly icon, and splash screen during boot
2014-10-24 Removed Chipkit IDE from repository -- this is too large and should be kept separately
2014-10-24 Minor revisions to motheboard (moved SD card over 2mm)
2014-10-24 Added plotly API, status widget, and connected to tile
2014-10-24 Added separate WiFi tile
2014-10-24 UpdateSensors() now also streams data to Plotly, if plotly is connected
2014-10-24 Added ability to disable plotly stream or wifi module after connected
2014-10-24 Found issue where Plotly streams will timeout after 2 minutes -- refactoring code
2014-10-25 Plotly interface rearchitected -- streams and graphs (composed of streams) are now properly encapsulated in structures, stream names are now supported, and the plotstream buffer is now defensively co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
2014-10-25 minor plotly changes/bug fixes
2014-10-25 Added units to plotly graph
2014-10-25 Added static (non streaming) plots to Plotly library. Spectrometer now saves plot when Select button is pressed on spectrometer graph view. Added radiation pulse width tile, and similar mechanism for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
2014-10-25 Added axis labels to static plotly plots
2014-10-26 Adding tiles for photosynthesis measurement
2014-10-26 Added chlorophyll symbol, and a lightweight non-ideal non-blocking averaging for the spectrometer
2014-10-28 Added laser cut patterns for case
2014-10-28 Minor changes to CC3000 library for larger buffers/speed
2014-10-28 Added Plotly library example
2014-10-28 Added Hamamtsu micro spectrometer example code
2014-10-28 Added radiation watch type 5 driver example
2014-10-28 Added CC3000 driver patch example from Adafruit, with pin configurations for Arducorder Mini
2014-10-28 Added partslists
2014-10-28 Added mag/imu rev0 gerbers
2014-10-28 Added lightning sensor board gerbers
2014-11-10 Changed partslists from txt to XLS format. Added formatting and source information for trickier parts
2014-11-10 minor cleanup
